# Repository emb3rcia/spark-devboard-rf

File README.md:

# spark-debug
# Navigation
- [About project](#about-project)
  - [Motivation for the project](#motivation-for-the-project)
  - [Humorous additions](#humorous-additions)
  - [Pin tables](#pin-tables)
  - [Development tools](#development-tools)
  - [Features](#features)
- [Images](#images)
- [License](#license)

# About project

spark-devboard-rf is RF focused devboard based on ESPRESSIF ESP32-WROVER-IE-N16R8 allowing Wi-Fi b/g/n, Bluetooth 4.2 Classic and Bluetooth 4.2 BLE communication using external u.FL antena

## Motivation for the project

spark-devboard-rf was created from boreness, but also as a stepping stone before using the same module in upcoming audio player of mine

## Pin functions

Pin functions are written on back of the PCB. Alternate functions can be found in [this datasheet](https://documentation.espressif.com/esp32-wrover-e_esp32-wrover-ie_datasheet_en.pdf)

## Usage

You use it as any other developement board. Important caveats are programming and powering the board.

### Programming

You need to program this board via UART interface specified on the back side of PCB. To enter flashing mode you need to hold BOOT button during power on or resetting the board

### Powering

Board can be either powered by 5x 3.3V pins on board, where you need to supply minimum of 500 mA for board to work properly, or via USB-C power-only port on board, where the pins become 3.3V output. **It is important to make sure that you are powering the board from only one supply method at the time**

## Directory overview

- 3D file of PCB is available in `/3D`
- KiCad project files are available in `/KiCad Project Files`
- Gerber files are available in `/Gerbers`

## Development tools

- KiCad for EDA work

## Features

- ESP32 module with 8MB PSRAM and 16MB flash
- u.FL antenna slot
- USB-C port for power
- Integrated 3.3V LDO

# Images

Schematic

PCB editor view

3D viewer top side

3D viewer bottom side

# License

## PCB / Schematic License

All files in `/PCB`, `/Schematic` and `/Gerbers` folders and their subsequent subfolders are licensed under the CERN Open Hardware License v2 (Weakly Reciprocal).

See `/Licenses/CERN-OHL.txt` for full terms.

## 3D files, images and documentation License

All files in `/3D`, `/Images` and `/Docs` folders and their subsequent subfolders are licensed under the CC-BY 4.0 License.

See `/Licenses/CC-BY-4.0.txt` for full terms

# BOM

|Name                          |Purpose                 |Quantity|Total Cost (USD)|Link                                                                                                     |Distributor|
|------------------------------|------------------------|--------|----------------|---------------------------------------------------------------------------------------------------------|-----------|
|PCB                           |PCB                     |5       |2.10            |                                                                                                         |JLCPCB     |
|MOLEX 206994-0100             |Antenna for connectivity|1       |2.38            |https://www.tme.eu/pl/details/2069940100/anteny-wifi-bluetooth/molex/206994-0100/                        |TME        |
|ESP32-WROVER-E-N16R8          |MCU module              |1       |6.40            |https://www.tme.eu/pl/details/esp32-wrover-e-16/moduly-iot-wifi-bluetooth/espressif/esp32-wrover-e-n16r8/|TME        |
|SHOU HAN TYPE-C 16PIN 2MD(073)|USB-C power port        |1       |0.00            |https://www.lcsc.com/product-detail/C2765186.html?s_z=n_C2765186                                         |LCSC       |

© 2026 emb3rcia

Hardware: CERN OHL v2
3D & Images: CC BY 4.0

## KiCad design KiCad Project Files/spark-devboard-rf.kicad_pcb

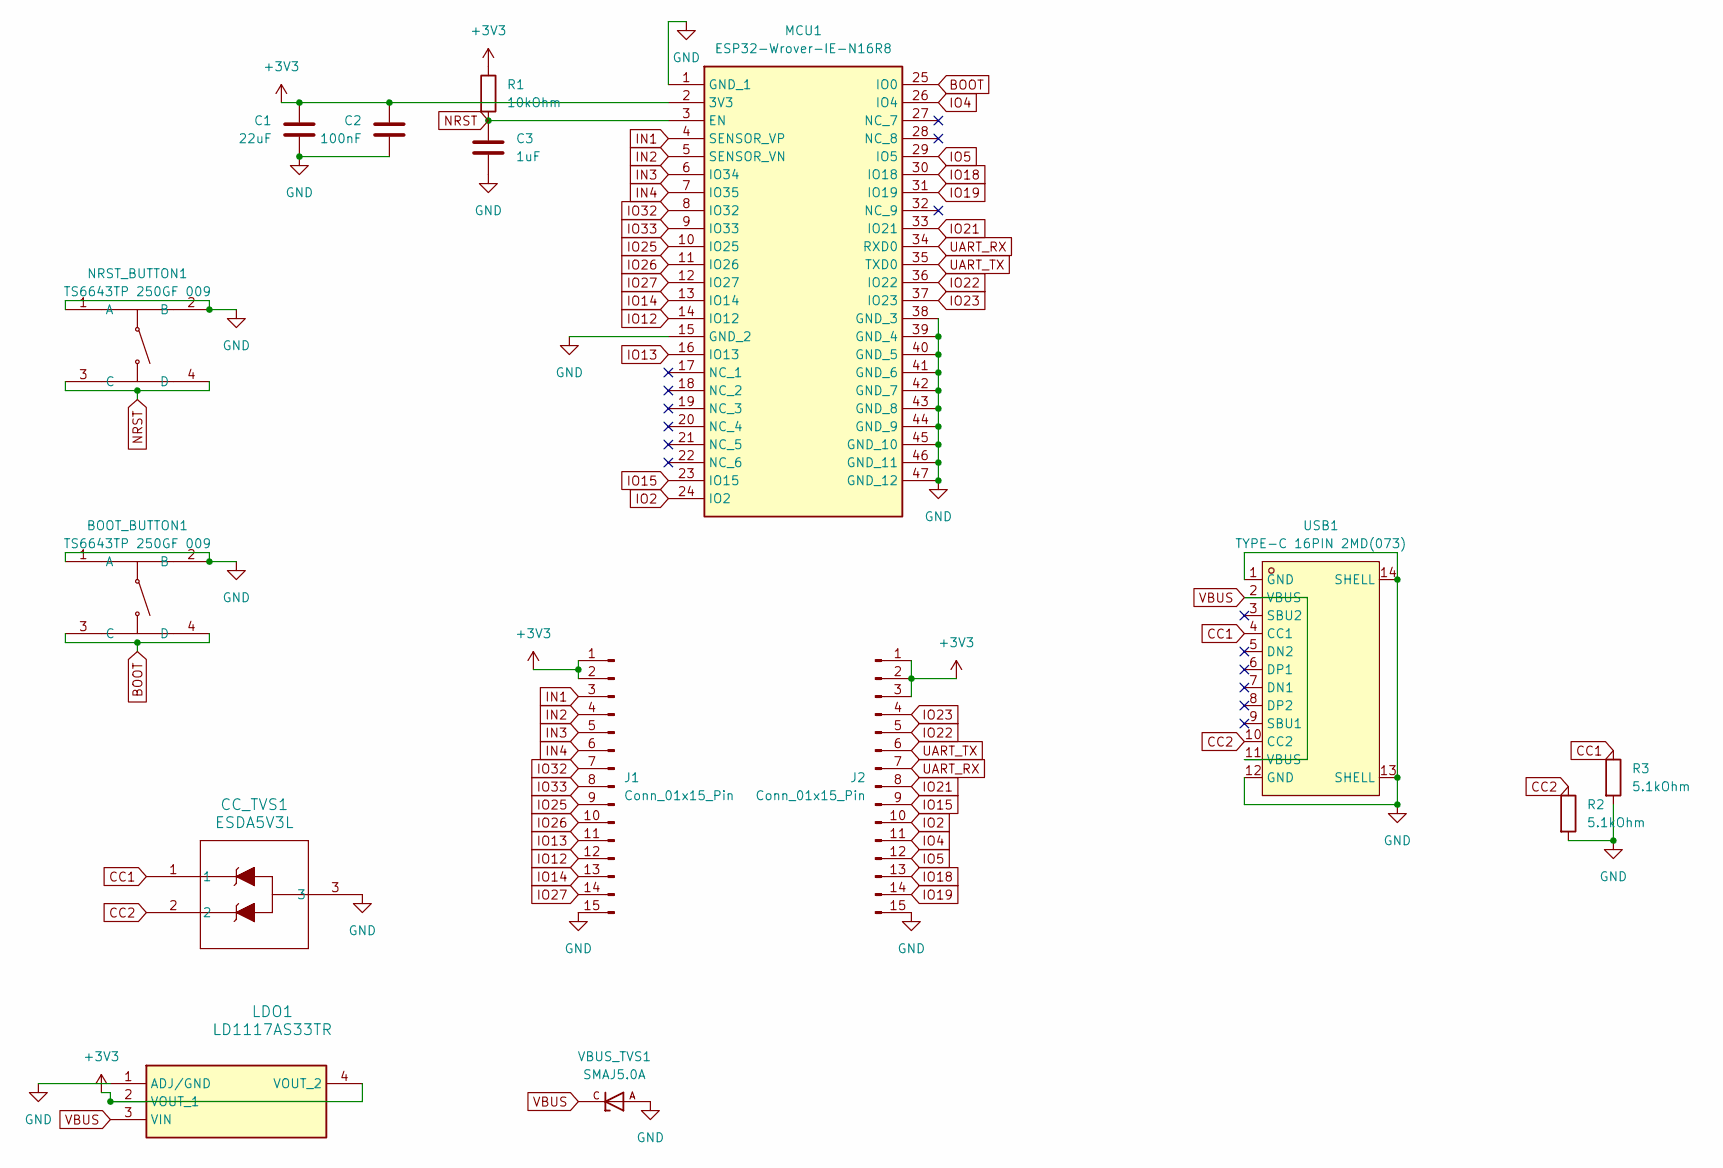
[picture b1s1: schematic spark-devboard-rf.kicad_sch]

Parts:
BOOT_BUTTON1: TS6643TP 250GF 009; SW-SMD_4P-L6.2-W6.0-P4.50-LS9.0; LCSC Part C5342967
C1: 22uF; C_0603_1608Metric
C2: 100nF; C_0603_1608Metric
C3: 1uF; C_0603_1608Metric
CC_TVS1: ESDA5V3L; SOT-23_STM
J1, J2: Conn_01x15_Pin; PinHeader_1x15_P2.54mm_Vertical
LDO1: LD1117AS33TR; SOT230P700X190-4N; Manufacturer_Part_Number LD1117AS33TR; Mouser Part Number 511-LD1117AS33
MCU1: ESP32-Wrover-IE-N16R8; ESP32WroverIEN16R8; Manufacturer_Part_Number ESP32-Wrover-IE-N16R8; Mouser Part Number 356-ESP32WRVIE2864UC
NRST_BUTTON1: TS6643TP 250GF 009; SW-SMD_4P-L6.2-W6.0-P4.50-LS9.0; LCSC Part C5342967
R1: 10kOhm; R_0603_1608Metric
R2, R3: 5.1kOhm; R_0603_1608Metric
USB1: TYPE-C 16PIN 2MD(073); USB-C-SMD_TYPE-C-6PIN-2MD-073; LCSC Part C2765186
VBUS_TVS1: SMAJ5.0A; DIOM4325X250N; PARTREV S2102

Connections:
+3V3: C1.1, C2.1, J1.1, J1.2, J2.1, J2.2, J2.3, LDO1.2 (VOUT_1), LDO1.4 (VOUT_2), MCU1.2 (3V3), R1.1
BOOT: BOOT_BUTTON1.3 (C), BOOT_BUTTON1.4 (D), MCU1.25 (IO0)
CC1: CC_TVS1.1, R3.1, USB1.4 (CC1)
CC2: CC_TVS1.2, R2.1, USB1.10 (CC2)
GND: BOOT_BUTTON1.1 (A), BOOT_BUTTON1.2 (B), C1.2, C2.2, C3.2, CC_TVS1.3, J1.15, J2.15, LDO1.1 (ADJ/GND), MCU1.1 (GND_1), MCU1.15 (GND_2), MCU1.38 (GND_3), MCU1.39 (GND_4), MCU1.40 (GND_5), MCU1.41 (GND_6), MCU1.42 (GND_7), MCU1.43 (GND_8), MCU1.44 (GND_9), MCU1.45 (GND_10), MCU1.46 (GND_11), MCU1.47 (GND_12), NRST_BUTTON1.1 (A), NRST_BUTTON1.2 (B), R2.2, R3.2, USB1.1 (GND), USB1.12 (GND), USB1.13 (SHELL), USB1.14 (SHELL), VBUS_TVS1.A
IN1: J1.3, MCU1.4 (SENSOR_VP)
IN2: J1.4, MCU1.5 (SENSOR_VN)
IN3: J1.5, MCU1.6 (IO34)
IN4: J1.6, MCU1.7 (IO35)
IO2: J2.10, MCU1.24 (IO2)
IO4: J2.11, MCU1.26 (IO4)
IO5: J2.12, MCU1.29 (IO5)
IO12: J1.12, MCU1.14 (IO12)
IO13: J1.11, MCU1.16 (IO13)
IO14: J1.13, MCU1.13 (IO14)
IO15: J2.9, MCU1.23 (IO15)
IO18: J2.13, MCU1.30 (IO18)
IO19: J2.14, MCU1.31 (IO19)
IO21: J2.8, MCU1.33 (IO21)
IO22: J2.5, MCU1.36 (IO22)
IO23: J2.4, MCU1.37 (IO23)
IO25: J1.9, MCU1.10 (IO25)
IO26: J1.10, MCU1.11 (IO26)
IO27: J1.14, MCU1.12 (IO27)
IO32: J1.7, MCU1.8 (IO32)
IO33: J1.8, MCU1.9 (IO33)
NRST: C3.1, MCU1.3 (EN), NRST_BUTTON1.3 (C), NRST_BUTTON1.4 (D), R1.2
UART_RX: J2.7, MCU1.34 (RXD0)
UART_TX: J2.6, MCU1.35 (TXD0)
VBUS: LDO1.3 (VIN), USB1.2 (VBUS), USB1.11 (VBUS), VBUS_TVS1.C

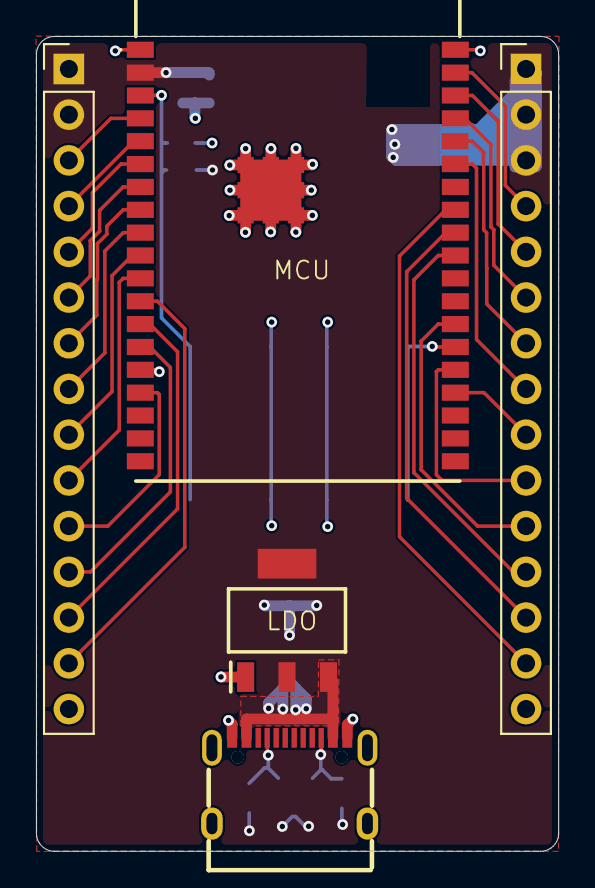
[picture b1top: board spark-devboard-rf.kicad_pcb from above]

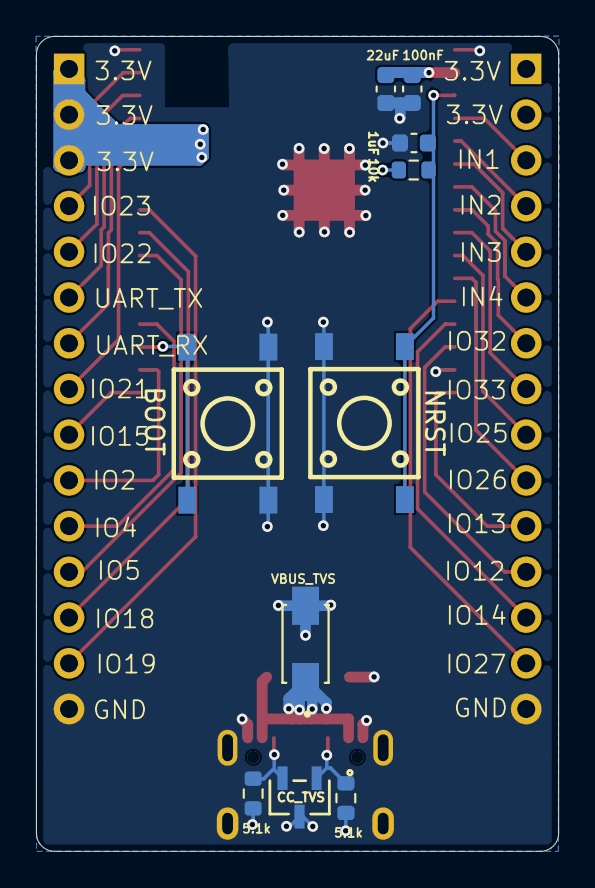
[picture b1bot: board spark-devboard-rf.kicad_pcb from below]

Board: 2 copper layers, 29.0 x 45.3 mm, 15 parts (10 on the bottom side), 30 nets.
